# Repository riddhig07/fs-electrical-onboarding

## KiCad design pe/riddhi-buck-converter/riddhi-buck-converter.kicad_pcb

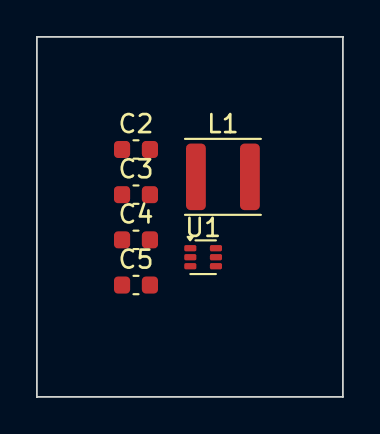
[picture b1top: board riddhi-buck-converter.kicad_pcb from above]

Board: 2 copper layers, 17.0 x 20.0 mm, 6 parts (0 on the bottom side), 4 nets, no tracks yet.

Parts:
C2, C4: 22uF; C_0603_1608Metric
C3: 10uF; C_0603_1608Metric
C5: 100nF; C_0603_1608Metric
L1: 2.2uH; L_Sunlord_SWPA4020S
U1: MP1477HGTF-Z; SOT-563

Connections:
+5V: C2.2, C4.2, L1.2, U1.4 (FB)
+12V: C3.2, U1.3 (IN), U1.5 (EN)
GND: C2.1, C3.1, C4.1, U1.1 (GND)
unnamed: C5.1, C5.2, L1.1, U1.2 (SW)
